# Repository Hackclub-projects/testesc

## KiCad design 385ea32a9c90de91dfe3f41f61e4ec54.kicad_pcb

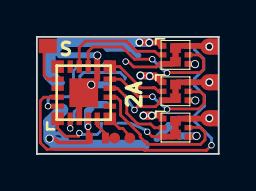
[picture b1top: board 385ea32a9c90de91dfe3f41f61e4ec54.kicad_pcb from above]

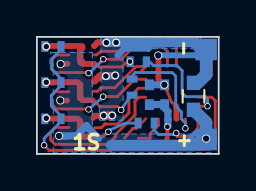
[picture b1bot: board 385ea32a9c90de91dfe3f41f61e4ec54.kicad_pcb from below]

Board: 2 copper layers, 10.1 x 6.5 mm, 22 parts (11 on the bottom side), 18 nets.

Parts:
C1: 47uf; C_0603
C2: 100n; C_0402_NoSilk
C3: 10uf; C_0402_NoSilk
J1: A; ESC_MOT_PAD
J2: B; ESC_MOT_PAD
J3: C; ESC_MOT_PAD
J4: RC; ESC_RC_PAD
J5: G; ESC_PWR_PAD
J6: V; ESC_PWR_PAD
J7: C2D; Test_PAD_0.6
J9: C2CK; Test_PAD_0.6
Q1, Q2, Q3: DUAL_NP; MicroFet-1.6
R1, R2, R3, R7: 1K; R_0402_NoSilk
R4, R5, R6: 10K; R_0402_NoSilk
U1: EFM8BB21; QFN20

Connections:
/M_A: J1.1, Q1.3, Q1.6, R1.2, R4.1
/M_B: J2.1, Q2.3, Q2.6, R2.2, R5.1
/M_C: J3.1, Q3.3, Q3.6, R3.2, R6.1
GND: C1.1, C2.1, C3.1, J5.1, Q1.1, Q2.1, Q3.1, U1.3, U1.12, U1.21
unnamed: J4.1, U1.17
unnamed: J7.1, U1.6
unnamed: J9.1, R7.2, U1.5
unnamed: Q1.2, U1.14
unnamed: Q1.5, U1.13
unnamed: Q2.2, U1.11
unnamed: Q2.5, U1.10
unnamed: Q3.2, U1.9
unnamed: Q3.5, U1.8
unnamed: R1.1, R2.1, R3.1, U1.19
unnamed: R4.2, U1.20
unnamed: R5.2, U1.2
unnamed: R6.2, U1.1
VCC: C1.2, C2.2, C3.2, J6.1, Q1.4, Q2.4, Q3.4, R7.1, U1.4

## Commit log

2026-02-20 Create WebXR room with interactive gamepad test TV
